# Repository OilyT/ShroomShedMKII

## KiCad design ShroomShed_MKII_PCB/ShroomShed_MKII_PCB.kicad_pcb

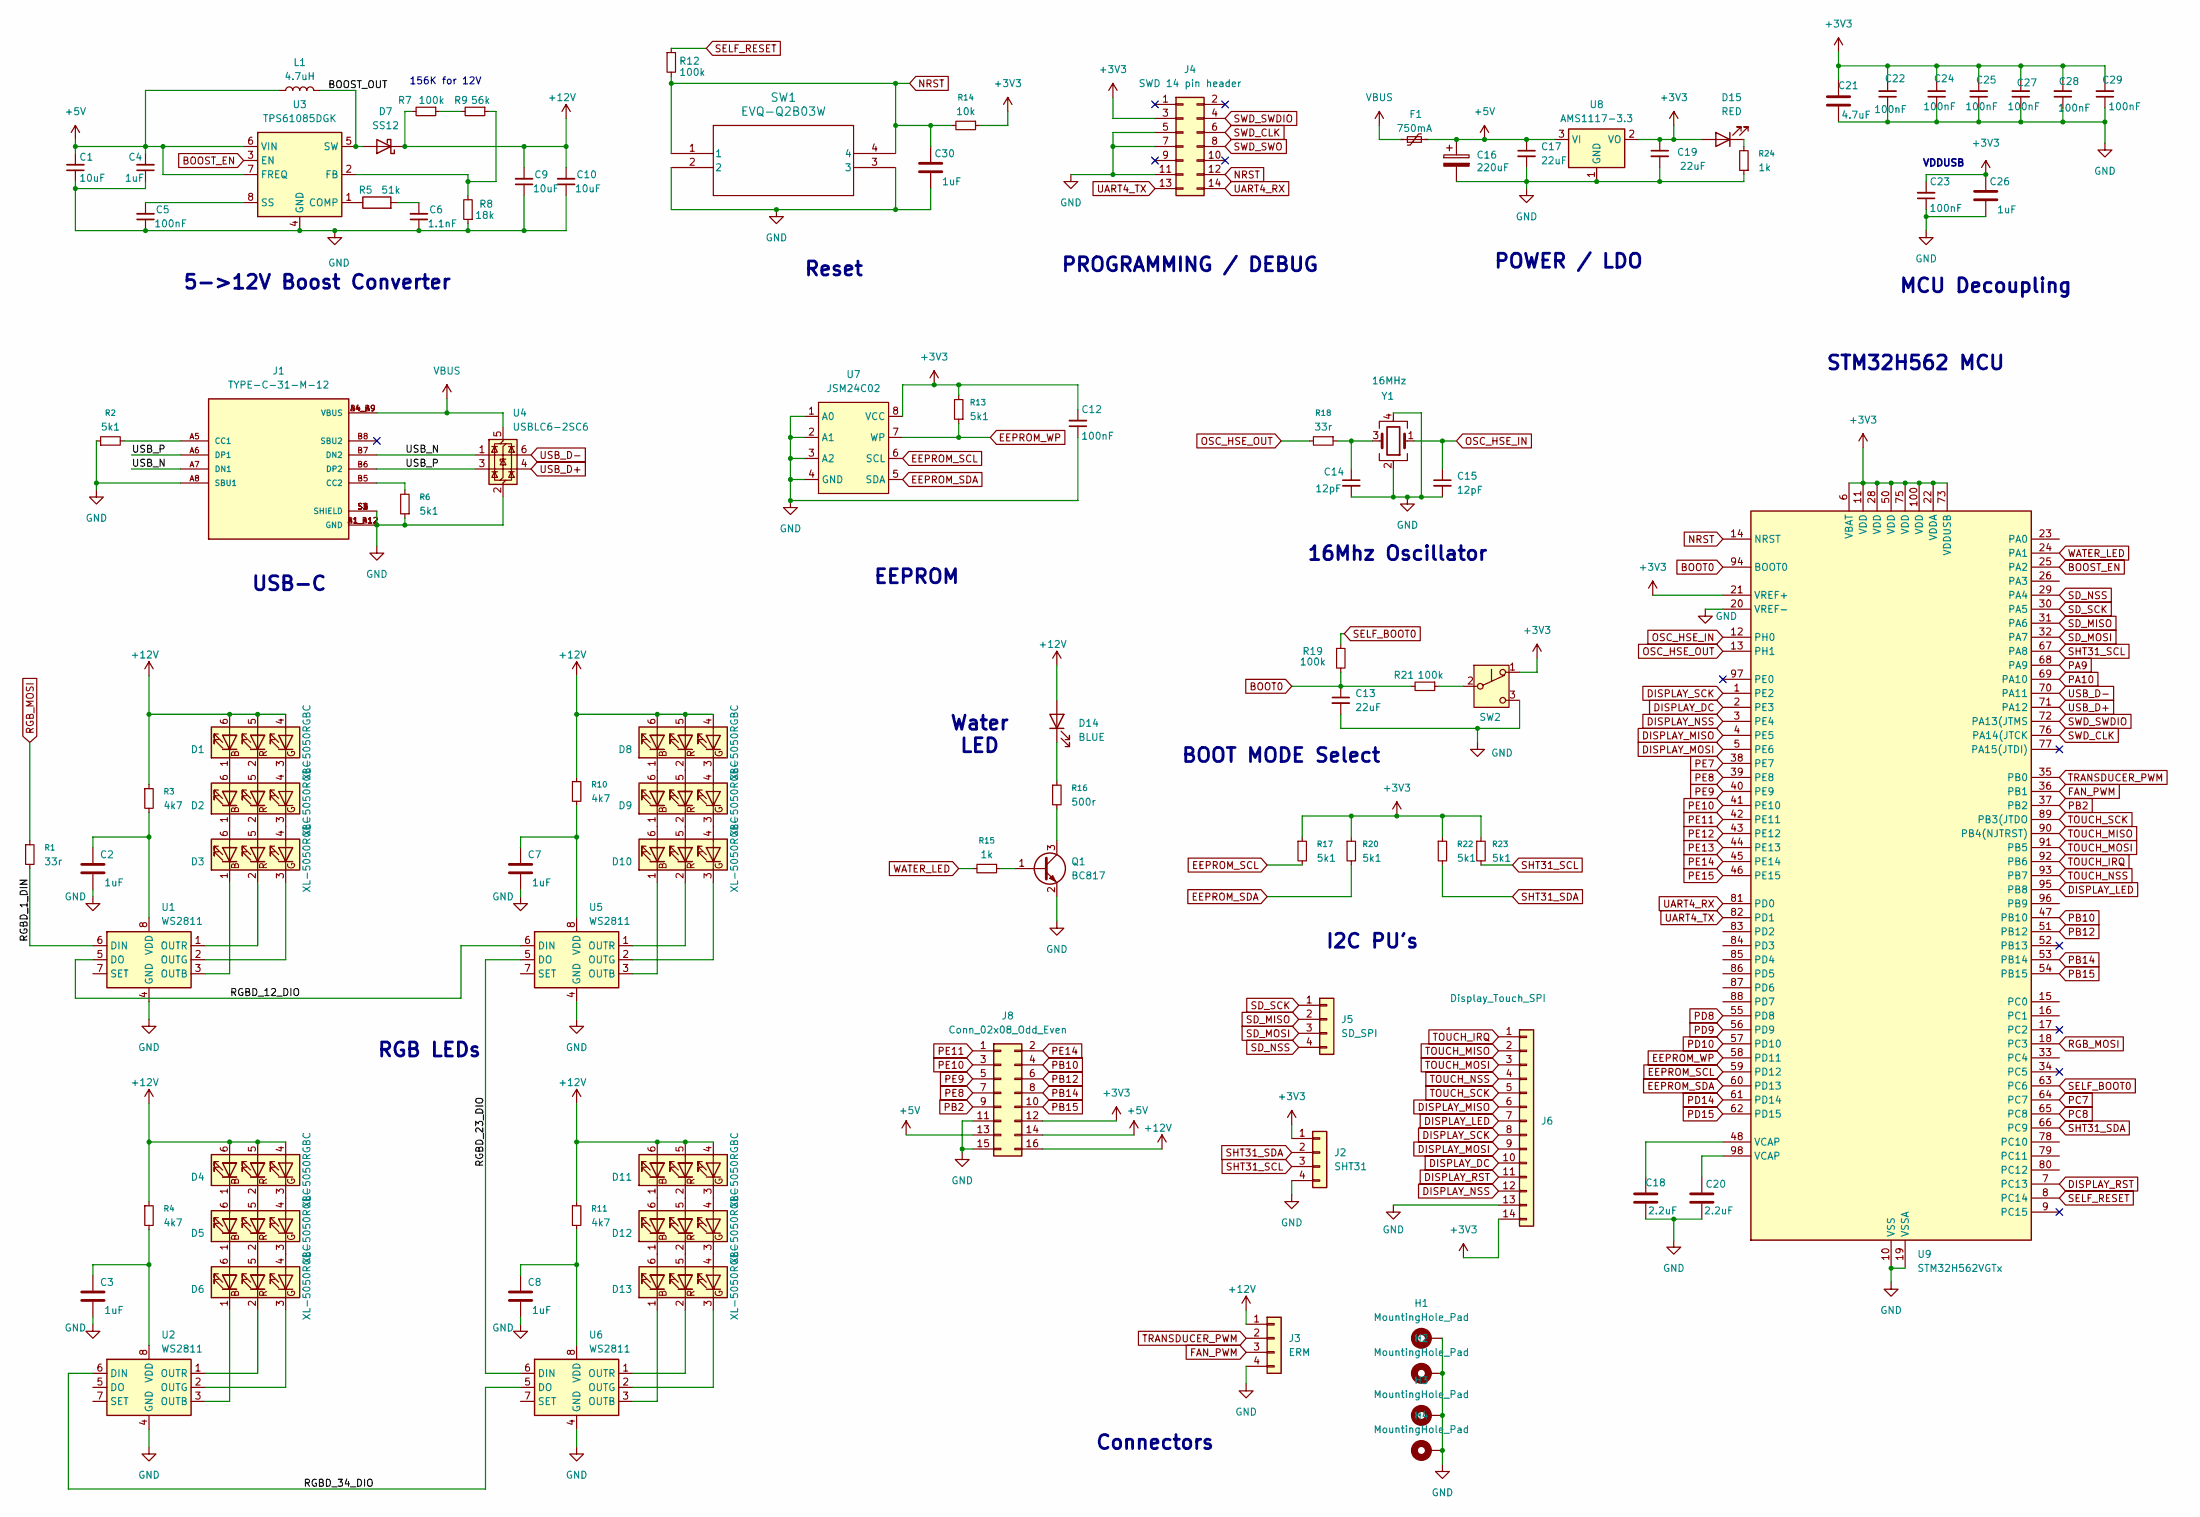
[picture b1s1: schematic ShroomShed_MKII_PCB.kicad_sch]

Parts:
C1, C9, C10: 10uF; C_0603_1608Metric
C2, C3, C4, C7, C8, C26, C30: 1uF; C_0603_1608Metric
C5, C12, C22, C23, C24, C25, C27, C28, C29: 100nF; C_0603_1608Metric
C6: 1.1nF; C_0603_1608Metric
C13, C17, C19: 22uF; C_0805_2012Metric
C14, C15: 12pF; C_0603_1608Metric
C16: 220uF; CP_Elec_6.3x5.4
C18, C20: 2.2uF; C_0603_1608Metric
C21: 4.7uF; C_0603_1608Metric
D1, D2, D3, D4, D5, D6, D8, D9, D10, D11, D12, D13: XL-5050RGBC; LED_RGB_5050-6
D7: SS12; D_SMA
D14: BLUE; LED_D4.0mm
D15: RED; LED_0603_1608Metric
F1: 750mA; Fuse_1210_3225Metric_Pad1.42x2.65mm_HandSolder
H1, H2, H3, H4: MountingHole_Pad; MountingHole_3.2mm_M3_Pad_Via
J1: TYPE-C-31-M-12; HRO_TYPE-C-31-M-12; PARTREV 2020.12.08
J2: SHT31; JST_XH_S4B-XH-A-1_1x04_P2.50mm_Horizontal; JLCPCB Part # C696092
J3: ERM; JST_XH_S4B-XH-A-1_1x04_P2.50mm_Horizontal; JLCPCB Part # C696092
J4: SWD 14 pin header; PinHeader_2x07_P1.27mm_Vertical_SMD
J5: SD_SPI; PinSocket_1x04_P2.54mm_Vertical; JLCPCB Part # C696092
J6: Display_Touch_SPI; PinSocket_1x14_P2.54mm_Vertical; JLCPCB Part # C505101
J8: Conn_02x08_Odd_Even; PinHeader_2x08_P2.54mm_Vertical
L1: 4.7uH; L_7.3x7.3_H4.5
Q1: BC817; SOT-23
R1, R18: 33r; R_0603_1608Metric
R2, R6, R13, R17, R20, R22, R23: 5k1; R_0603_1608Metric
R3, R4, R10, R11: 4k7; R_0603_1608Metric
R5: 51k; R_0603_1608Metric
R7, R12, R19, R21: 100k; R_0603_1608Metric
R8: 18k; R_0603_1608Metric
R9: 56k; R_0603_1608Metric
R14: 10k; R_0603_1608Metric
R15, R24: 1k; R_0603_1608Metric
R16: 500r; R_0603_1608Metric
SW1: EVQ-Q2B03W; EVQQ2_3_PAN
SW2: BOOT SELECT; MST-22D18G2 3J
U1, U2, U5, U6: WS2811; SOIC-8_3.9x4.9mm_P1.27mm
U3: TPS61085DGK; VSSOP-8_3x3mm_P0.65mm
U4: USBLC6-2SC6; SOT-23-6
U7: JSM24C02; SOIC-8_3.9x4.9mm_P1.27mm
U8: AMS1117-3.3; SOT-223-3_TabPin2
U9: STM32H562VGTx; LQFP-100_14x14mm_P0.5mm
Y1: 16MHz; Crystal_SMD_3225-4Pin_3.2x2.5mm; part# C13738

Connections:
+3V3: C12.2, C19.1, C21.1, C22.2, C23.2, C24.2, C25.2, C26.1, C27.2, C28.2, C29.2, D15.2 (A), J2.1, J4.3, J6.14, J8.12, R13.2, R14.1, R17.1, R20.1, R22.1, R23.1, SW2.1 (A), U7.8 (VCC), U8.2 (VO), U9.6 (VBAT), U9.11 (VDD), U9.21 (VREF+), U9.22 (VDDA), U9.28 (VDD), U9.50 (VDD), U9.73 (VDDUSB), U9.75 (VDD), U9.100 (VDD)
+5V: C1.2, C4.2, C16.1, C17.1, F1.2, J8.13, J8.14, L1.1, U3.6 (VIN), U3.7 (FREQ), U8.3 (VI)
+12V: C9.2, C10.2, D1.4 (BA), D1.5 (GA), D1.6 (RA), D4.4 (BA), D4.5 (GA), D4.6 (RA), D7.1 (K), D8.4 (BA), D8.5 (GA), D8.6 (RA), D11.4 (BA), D11.5 (GA), D11.6 (RA), D14.2 (A), J3.1, J8.16, R3.1, R4.1, R7.2, R10.1, R11.1
/BOOST_OUT: D7.2 (A), L1.2, U3.5 (SW)
/RGBD_1_DIN: R1.2, U1.6 (DIN)
/RGBD_12_DIO: U1.5 (DO), U5.6 (DIN)
/RGBD_23_DIO: U5.5 (DO), U6.6 (DIN)
/RGBD_34_DIO: U2.6 (DIN), U6.5 (DO)
/USB_N: J1.A7 (DN1), J1.B7 (DN2), U4.1 (I/O1)
/USB_P: J1.A6 (DP1), J1.B6 (DP2), U4.3 (I/O2)
BOOST_EN: U3.3 (EN), U9.25 (PA2)
BOOT0: C13.1, R19.2, R21.2, U9.94 (BOOT0)
DISPLAY_DC: J6.10, U9.2 (PE3)
DISPLAY_LED: J6.7, U9.95 (PB8)
DISPLAY_MISO: J6.6, U9.4 (PE5)
DISPLAY_MOSI: J6.9, U9.5 (PE6)
DISPLAY_NSS: J6.12, U9.3 (PE4)
DISPLAY_RST: J6.11, U9.7 (PC13)
DISPLAY_SCK: J6.8, U9.1 (PE2)
EEPROM_SCL: R17.2, U7.6 (SCL), U9.59 (PD12)
EEPROM_SDA: R20.2, U7.5 (SDA), U9.60 (PD13)
EEPROM_WP: R13.1, U7.7 (WP), U9.58 (PD11)
FAN_PWM: J3.3, U9.36 (PB1)
GND: C1.1, C2.2, C3.2, C4.1, C5.1, C6.1, C7.2, C8.2, C9.1, C10.1, C12.1, C13.2, C14.2, C15.2, C16.2, C17.2, C18.1, C19.2, C20.1, C21.2, C22.1, C23.1, C24.1, C25.1, C26.2, C27.1, C28.1, C29.1, C30.2, H1.1 (1_1), H2.1 (1_1), H3.1 (1_1), H4.1 (1_1), J1.A1_B12 (GND), J1.A8 (SBU1), J1.B1_A12 (GND), J1.S1 (SHIELD), J1.S2 (SHIELD), J1.S3 (SHIELD), J1.S4 (SHIELD), J2.4, J3.4, J4.5, J4.7, J4.11, J6.13, J8.11, J8.15, Q1.2 (E), R2.1, R6.1, R8.1, R24.1, SW1.2, SW1.3, SW2.3 (C), U1.4 (GND), U2.4 (GND), U3.4 (GND), U4.2 (GND), U5.4 (GND), U6.4 (GND), U7.1 (A0), U7.2 (A1), U7.3 (A2), U7.4 (GND), U8.1 (GND), U9.10 (VSS), U9.19 (VSSA), U9.20 (VREF-), U9.27 (VSS), U9.49 (VSS), U9.74 (VSS), U9.99 (VSS), Y1.2, Y1.4
NRST: C30.1, J4.12, R12.2, R14.2, SW1.1, SW1.4, U9.14 (NRST)
unnamed: C6.2, R5.2
unnamed: C14.1, R18.1, Y1.3
unnamed: C18.2, U9.48 (VCAP)
unnamed: C20.2, U9.98 (VCAP)
unnamed: D1.3 (BK), D2.4 (BA)
unnamed: D1.2 (GK), D2.5 (GA)
unnamed: D1.1 (RK), D2.6 (RA)
unnamed: D2.3 (BK), D3.4 (BA)
unnamed: D2.2 (GK), D3.5 (GA)
unnamed: D2.1 (RK), D3.6 (RA)
unnamed: D3.3 (BK), U1.2 (OUTG)
unnamed: D3.2 (GK), U1.1 (OUTR)
unnamed: D3.1 (RK), U1.3 (OUTB)
unnamed: D4.3 (BK), D5.4 (BA)
unnamed: D4.2 (GK), D5.5 (GA)
unnamed: D4.1 (RK), D5.6 (RA)
unnamed: D5.3 (BK), D6.4 (BA)
unnamed: D5.2 (GK), D6.5 (GA)
unnamed: D5.1 (RK), D6.6 (RA)
unnamed: D6.3 (BK), U2.2 (OUTG)
unnamed: D6.2 (GK), U2.1 (OUTR)
unnamed: D6.1 (RK), U2.3 (OUTB)
unnamed: D8.3 (BK), D9.4 (BA)
unnamed: D8.2 (GK), D9.5 (GA)
unnamed: D8.1 (RK), D9.6 (RA)
unnamed: D9.3 (BK), D10.4 (BA)
unnamed: D10.3 (BK), U5.2 (OUTG)
unnamed: D9.2 (GK), D10.5 (GA)
unnamed: D10.2 (GK), U5.1 (OUTR)
unnamed: D9.1 (RK), D10.6 (RA)
unnamed: D10.1 (RK), U5.3 (OUTB)
unnamed: D11.3 (BK), D12.4 (BA)
unnamed: D11.2 (GK), D12.5 (GA)
unnamed: D11.1 (RK), D12.6 (RA)
unnamed: D12.3 (BK), D13.4 (BA)
unnamed: D12.2 (GK), D13.5 (GA)
unnamed: D12.1 (RK), D13.6 (RA)
unnamed: D13.3 (BK), U6.2 (OUTG)
unnamed: D13.2 (GK), U6.1 (OUTR)
unnamed: D13.1 (RK), U6.3 (OUTB)
unnamed: D14.1 (K), R16.1
unnamed: D15.1 (K), R24.2
unnamed: J1.A5 (CC1), R2.2
unnamed: J1.B5 (CC2), R6.2
unnamed: Q1.1 (B), R15.1
unnamed: Q1.3 (C), R16.2
unnamed: R7.1, R9.2
unnamed: R21.1, SW2.2 (B)
unnamed: C2.1, R3.2, U1.8 (VDD)
unnamed: C3.1, R4.2, U2.8 (VDD)
unnamed: R5.1, U3.1 (COMP)
unnamed: R8.2, R9.1, U3.2 (FB)
unnamed: C5.2, U3.8 (SS)
unnamed: C7.1, R10.2, U5.8 (VDD)
unnamed: C8.1, R11.2, U6.8 (VDD)
OSC_HSE_IN: C15.1, U9.12 (PH0), Y1.1
OSC_HSE_OUT: R18.2, U9.13 (PH1)
PA9: U9.68 (PA9)
PA10: U9.69 (PA10)
PB2: J8.9, U9.37 (PB2)
PB10: J8.4, U9.47 (PB10)
PB12: J8.6, U9.51 (PB12)
PB14: J8.8, U9.53 (PB14)
PB15: J8.10, U9.54 (PB15)
PC7: U9.64 (PC7)
PC8: U9.65 (PC8)
PD8: U9.55 (PD8)
PD9: U9.56 (PD9)
PD10: U9.57 (PD10)
PD14: U9.61 (PD14)
PD15: U9.62 (PD15)
PE7: U9.38 (PE7)
PE8: J8.7, U9.39 (PE8)
PE9: J8.5, U9.40 (PE9)
PE10: J8.3, U9.41 (PE10)
PE11: J8.1, U9.42 (PE11)
PE12: U9.43 (PE12)
PE13: U9.44 (PE13)
PE14: J8.2, U9.45 (PE14)
PE15: U9.46 (PE15)
RGB_MOSI: R1.1, U9.18 (PC3)
SD_MISO: J5.2, U9.31 (PA6)
SD_MOSI: J5.3, U9.32 (PA7)
SD_NSS: J5.4, U9.29 (PA4)
SD_SCK: J5.1, U9.30 (PA5)
SELF_BOOT0: R19.1, U9.63 (PC6)
SELF_RESET: R12.1, U9.8 (PC14)
SHT31_SCL: J2.3, R23.2, U9.67 (PA8)
SHT31_SDA: J2.2, R22.2, U9.66 (PC9)
SWD_CLK: J4.6, U9.76 (PA14(JTCK)
SWD_SWDIO: J4.4, U9.72 (PA13(JTMS)
SWD_SWO: J4.8
TOUCH_IRQ: J6.1, U9.92 (PB6)
TOUCH_MISO: J6.2, U9.90 (PB4(NJTRST))
TOUCH_MOSI: J6.3, U9.91 (PB5)
TOUCH_NSS: J6.4, U9.93 (PB7)
TOUCH_SCK: J6.5, U9.89 (PB3(JTDO)
TRANSDUCER_PWM: J3.2, U9.35 (PB0)
UART4_RX: J4.14, U9.81 (PD0)
UART4_TX: J4.13, U9.82 (PD1)
USB_D+: U4.4 (I/O2), U9.71 (PA12)
USB_D-: U4.6 (I/O1), U9.70 (PA11)
VBUS: F1.1, J1.A4_B9 (VBUS), J1.B4_A9 (VBUS), U4.5 (VBUS)
WATER_LED: R15.2, U9.24 (PA1)

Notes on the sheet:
STM32H562 MCU
16Mhz Oscillator
USB-C
BOOT MODE Select
MCU Decoupling
5->12V Boost Converter
RGB LEDs
POWER / LDO
Water LED
I2C PU's
PROGRAMMING / DEBUG
Connectors
Reset
VDDUSB
EEPROM
156K for 12V

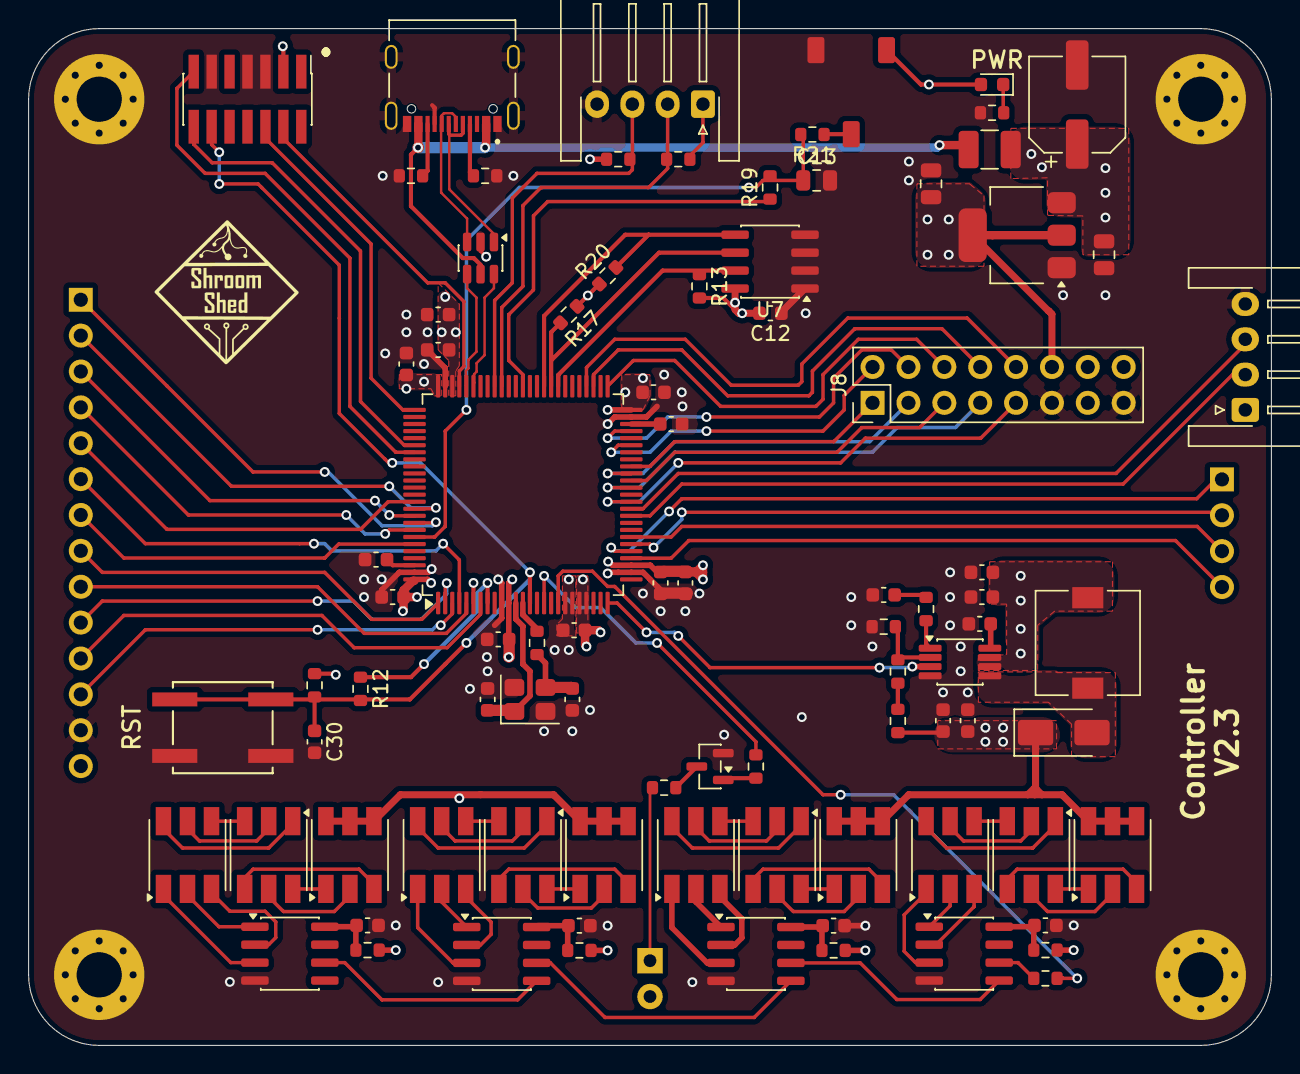
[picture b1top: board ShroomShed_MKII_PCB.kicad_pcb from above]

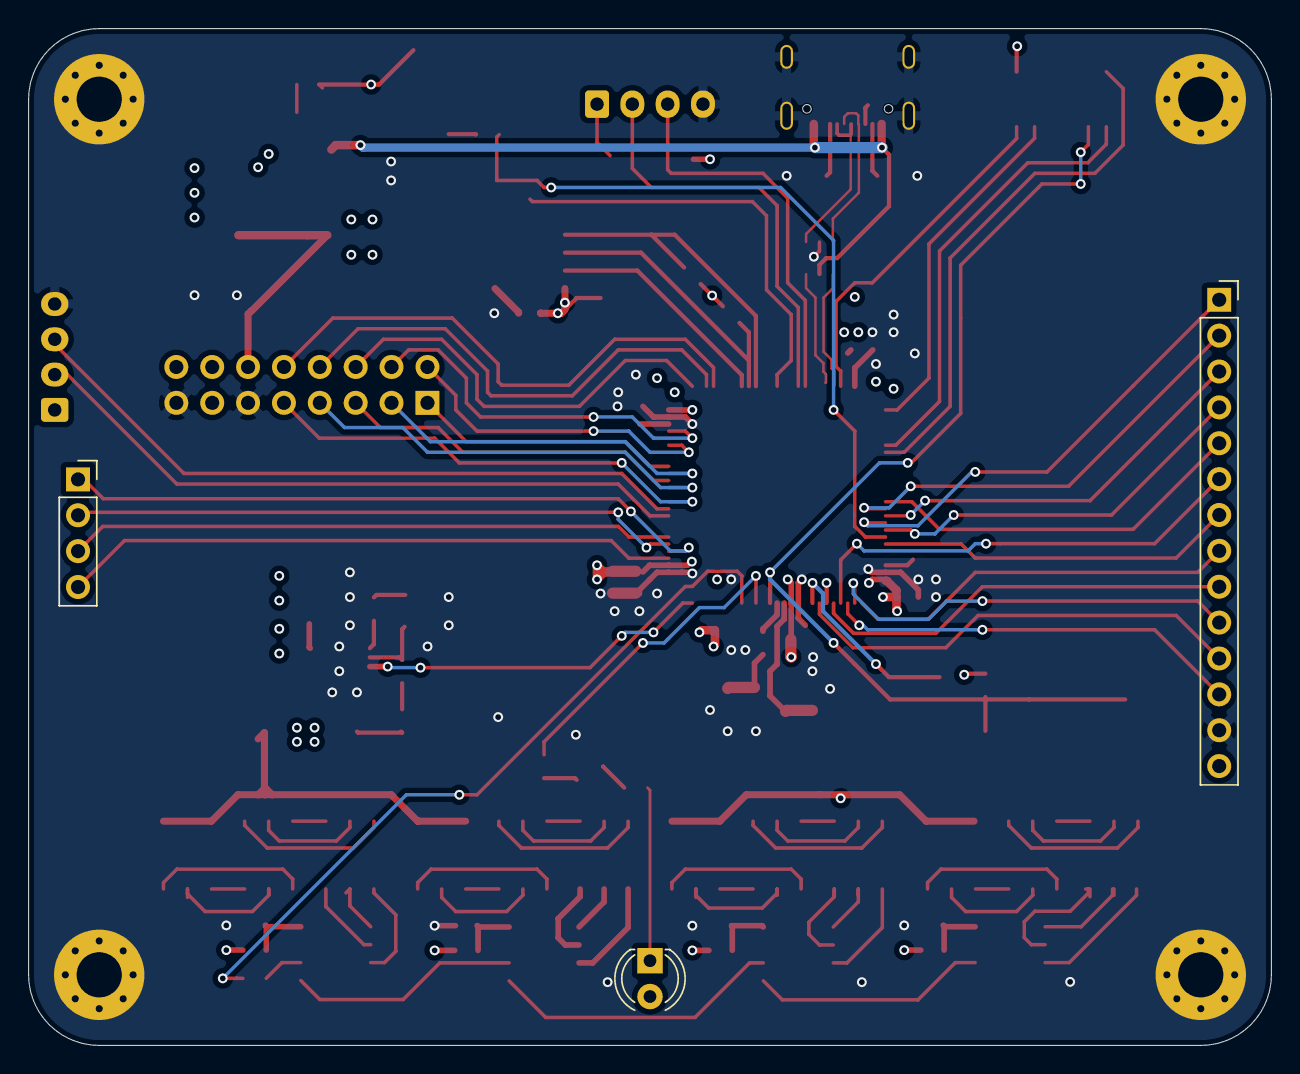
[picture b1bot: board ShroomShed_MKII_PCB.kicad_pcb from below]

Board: 4 copper layers, 88.0 x 72.0 mm, 94 parts (3 on the bottom side), 115 nets.

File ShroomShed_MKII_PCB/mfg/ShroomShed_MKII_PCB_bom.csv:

"Reference","Qty","Value","DNP","Exclude from BOM","Exclude from Board","Footprint","Datasheet","P#"
"C1,C9,C10","3","10uF","","","","Capacitor_SMD:C_0603_1608Metric","~",""
"C2,C3,C4,C7,C8,C25","6","1uF","","","","Capacitor_SMD:C_0603_1608Metric","~",""
"C5,C11,C12,C21,C22,C23,C24,C26,C27,C28","10","100nF","","","","Capacitor_SMD:C_0603_1608Metric","~",""
"C6","1","1.1nF","","","","Capacitor_SMD:C_0603_1608Metric","~",""
"C13,C14","2","12pF","","","","Capacitor_SMD:C_0603_1608Metric","~",""
"C15","1","470uF","","","","Capacitor_SMD:CP_Elec_6.3x7.7","","C2977552"
"C16,C17","2","22uF","","","","Capacitor_SMD:C_0805_2012Metric","~",""
"C18,C19","2","2.2uF","","","","Capacitor_SMD:C_0603_1608Metric","~",""
"C20","1","4.7uF","","","","Capacitor_SMD:C_0603_1608Metric","~",""
"D1,D2,D3,D4,D5,D6,D8,D9,D10,D11,D12,D13","12","XL-5050RGBC","","","","LED_SMD:LED_RGB_5050-6","~","C784540"
"D7","1","SS12","","","","Diode_SMD:D_SMA","https://www.vishay.com/docs/88746/ss12.pdf",""
"D14","1","BLUE","","","","LED_THT:LED_D4.0mm","~",""
"D15","1","RED","","","","LED_SMD:LED_0603_1608Metric","~",""
"F1","1","750mA","","","","Fuse:Fuse_1210_3225Metric_Pad1.42x2.65mm_HandSolder","~","C20805"
"H1,H2,H3,H4","4","MountingHole_Pad","","Excluded from BOM","","MountingHole:MountingHole_3.2mm_M3_Pad","~",""
"J1","1","TYPE-C-31-M-12","","","","footprints:HRO_TYPE-C-31-M-12","",""
"J2","1","UART","","","","Connector_PinHeader_2.00mm:PinHeader_1x04_P2.00mm_Vertical","~",""
"J3","1","Inputs","","","","Connector_JST:JST_XH_B6B-XH-A_1x06_P2.50mm_Vertical","~",""
"J4","1","SHT31","","","","Connector_JST:JST_XH_S4B-XH-A-1_1x04_P2.50mm_Horizontal","~",""
"J5","1","SWD 14 pin header","","","","Connector_PinHeader_1.27mm:PinHeader_2x07_P1.27mm_Vertical_SMD","~","C6332251"
"J6","1","ERM","","","","Connector_JST:JST_XH_S4B-XH-A-1_1x04_P2.50mm_Horizontal","~",""
"J7","1","SD_SPI","","","","Connector_PinSocket_2.54mm:PinSocket_1x04_P2.54mm_Vertical","~",""
"J8","1","Display_Touch_SPI","","","","Connector_PinSocket_2.54mm:PinSocket_1x14_P2.54mm_Vertical","~",""
"L1","1","4.7uH","","","","Inductor_SMD:L_7.3x7.3_H4.5","~",""
"Q1","1","BC817","","","","Package_TO_SOT_SMD:SOT-23","https://www.onsemi.com/pub/Collateral/BC818-D.pdf",""
"R1,R18","2","33r","","","","Resistor_SMD:R_0603_1608Metric","~",""
"R2,R6,R12,R13","4","5k1","","","","Resistor_SMD:R_0603_1608Metric","~",""
"R3,R4,R10,R11","4","4k7","","","","Resistor_SMD:R_0603_1608Metric","~",""
"R5","1","51k","","","","Resistor_SMD:R_0603_1608Metric","~",""
"R7","1","100k","","","","Resistor_SMD:R_0603_1608Metric","~",""
"R8","1","18k","","","","Resistor_SMD:R_0603_1608Metric","~",""
"R9","1","56k","","","","Resistor_SMD:R_0603_1608Metric","~",""
"R14,R17,R19,R20","4","10k","","","","Resistor_SMD:R_0603_1608Metric","~",""
"R15,R21","2","1k","","","","Resistor_SMD:R_0603_1608Metric","~",""
"R16","1","500r","","","","Resistor_SMD:R_0603_1608Metric","~",""
"SW1","1","EVQ-Q2B03W","","","","footprints:EVQQ2_3_PAN","EVQ-Q2B03W",""
"SW2","1","BOOT SELECT","","","","Button_Switch_SMD:SW_SPDT_Shouhan_MSK12C02","~","C431540"
"U1,U2,U5,U6","4","WS2811","","","","Package_SO:SOIC-8_3.9x4.9mm_P1.27mm","https://cdn-shop.adafruit.com/datasheets/WS2811.pdf",""
"U3","1","TPS61085DGK","","","","Package_SO:VSSOP-8_3x3mm_P0.65mm","https://www.ti.com/lit/ds/symlink/tps61085.pdf",""
"U4","1","USBLC6-2SC6","","","","Package_TO_SOT_SMD:SOT-23-6","https://www.st.com/resource/en/datasheet/usblc6-2.pdf",""
"U7","1","ENS210","","","","Package_DFN_QFN:AMS_QFN-4-1EP_2x2mm_P0.95mm_EP0.7x1.6mm","http://ams.com/eng/Products/Environmental-Sensors/Relative-H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",""
"U8","1","AMS1117-3.3","","","","Package_TO_SOT_SMD:SOT-223-3_TabPin2","http://www.advanced-monolithic.com/pdf/ds1117.pdf",""
"U9","1","STM32H562VGTx","","","","Package_QFP:LQFP-100_14x14mm_P0.5mm","https://www.st.com/resource/en/datasheet/stm32h562vg.pdf",""
"Y1","1","16MHz","","","","Crystal:Crystal_SMD_3225-4Pin_3.2x2.5mm","~",""

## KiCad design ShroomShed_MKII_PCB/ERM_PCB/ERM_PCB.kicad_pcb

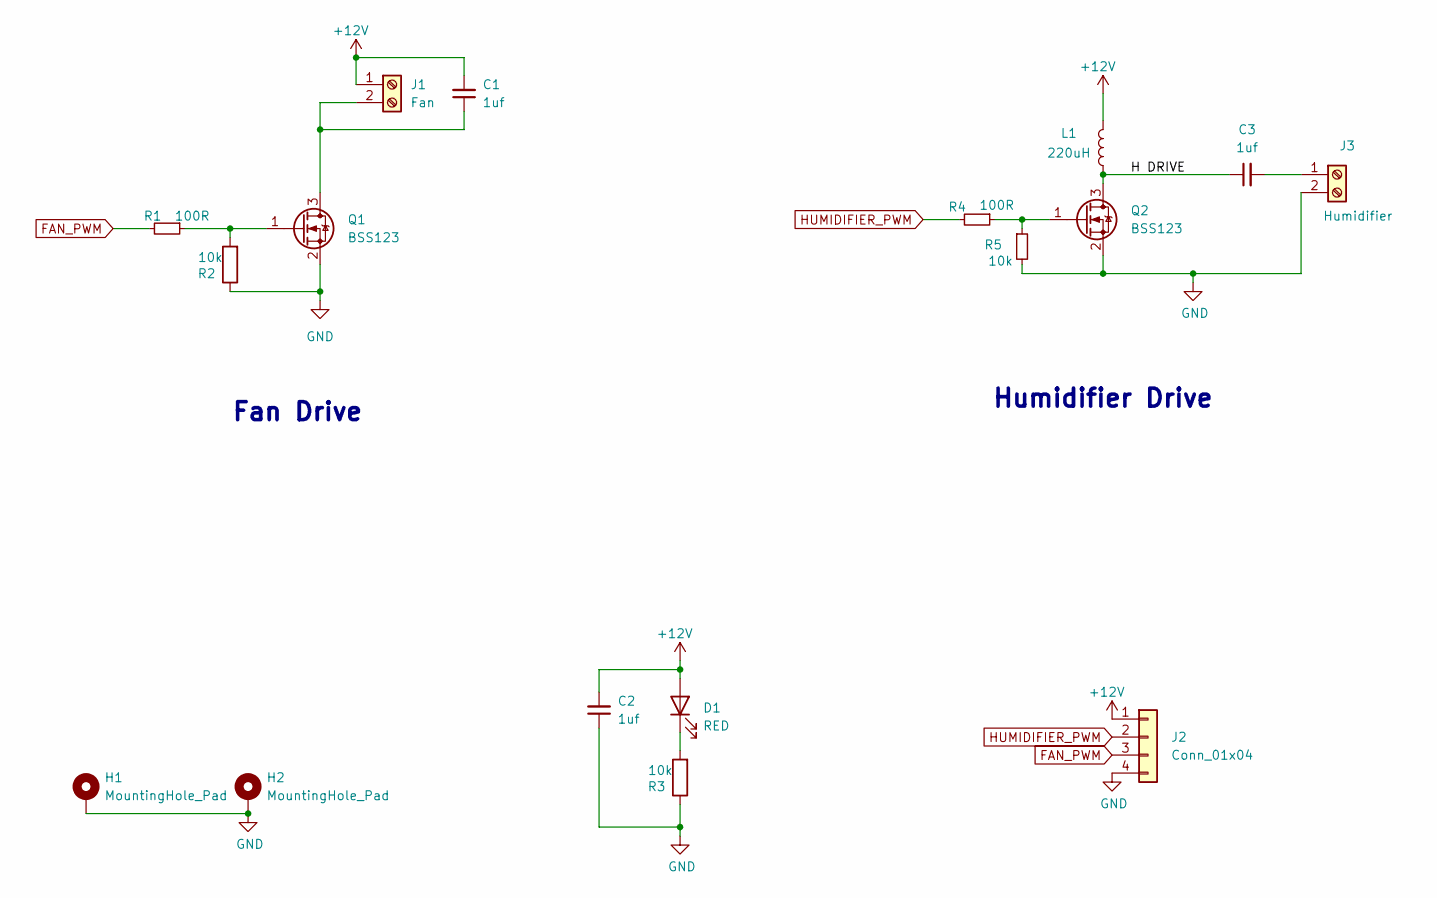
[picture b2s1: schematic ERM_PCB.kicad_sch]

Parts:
C1, C2, C3: 1uf; C_0603_1608Metric
D1: RED; LED_0603_1608Metric
H1, H2: MountingHole_Pad; MountingHole_3.2mm_M3_Pad
J1: Fan; JST_XH_S2B-XH-A-1_1x02_P2.50mm_Horizontal
J2: Conn_01x04; JST_XH_S4B-XH-A-1_1x04_P2.50mm_Horizontal
J3: Humidifier; JST_PH_S2B-PH-K_1x02_P2.00mm_Horizontal
L1: 220uH; SMDRH104R
Q1, Q2: BSS123; SOT-23
R1, R4: 100R; R_0603_1608Metric
R2, R3, R5: 10k; R_0603_1608Metric

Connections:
+12V: C1.2, C2.2, D1.2 (A), J1.1, J2.1, L1.2
/H DRIVE: C3.1, L1.1, Q2.3 (D)
FAN_PWM: J2.3, R1.2
GND: C2.1, H1.1 (1_1), H2.1 (1_1), J2.4, J3.2, Q1.2 (S), Q2.2 (S), R2.1, R3.1, R5.2
HUMIDIFIER_PWM: J2.2, R4.2
unnamed: D1.1 (K), R3.2
unnamed: C1.1, J1.2, Q1.3 (D)
unnamed: C3.2, J3.1
unnamed: Q1.1 (G), R1.1, R2.2
unnamed: Q2.1 (G), R4.1, R5.1

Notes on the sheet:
Humidifier Drive
Fan Drive

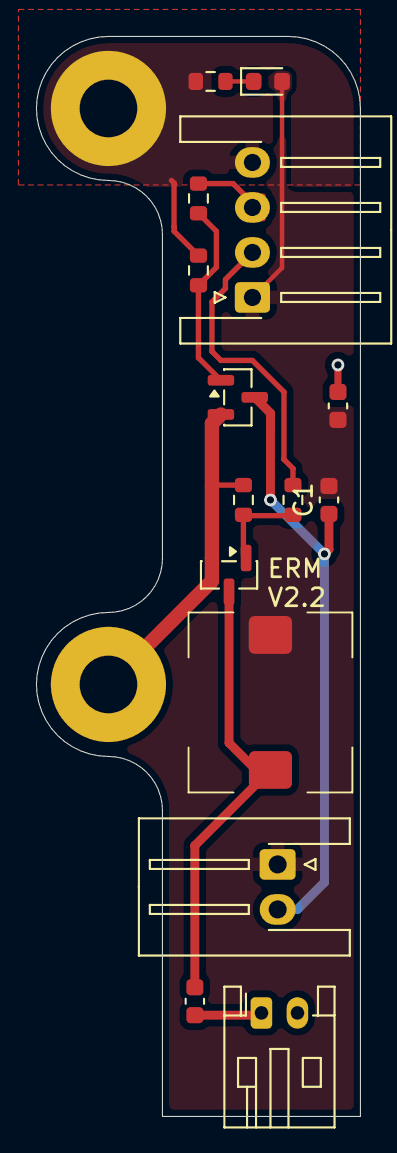
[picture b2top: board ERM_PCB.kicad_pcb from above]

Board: 2 copper layers, 18.0 x 60.0 mm, 17 parts (0 on the bottom side), 10 nets.

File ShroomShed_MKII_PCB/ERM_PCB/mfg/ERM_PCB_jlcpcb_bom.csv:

Comment,Designator,Footprint,JLCPCB Part #?optional?
1uf,"C1,C2",Capacitor_SMD:C_0603_1608Metric,
RED,D1,LED_SMD:LED_0603_1608Metric,
Fan,J1,Connector_JST:JST_XH_S2B-XH-A-1_1x02_P2.50mm_Horizontal,
Humidifier,J2,Connector_JST:JST_PH_S2B-PH-K_1x02_P2.00mm_Horizontal,
Conn_01x04,J3,Connector_JST:JST_XH_S4B-XH-A-1_1x04_P2.50mm_Horizontal,
220uH,L1,footprints:SMDRH104R,C3000009
BSS123,"Q1,Q2",Package_TO_SOT_SMD:SOT-23,C8491
100R,"R1,R3",Resistor_SMD:R_0603_1608Metric,
10k,"R2,R4,R5",Resistor_SMD:R_0603_1608Metric,

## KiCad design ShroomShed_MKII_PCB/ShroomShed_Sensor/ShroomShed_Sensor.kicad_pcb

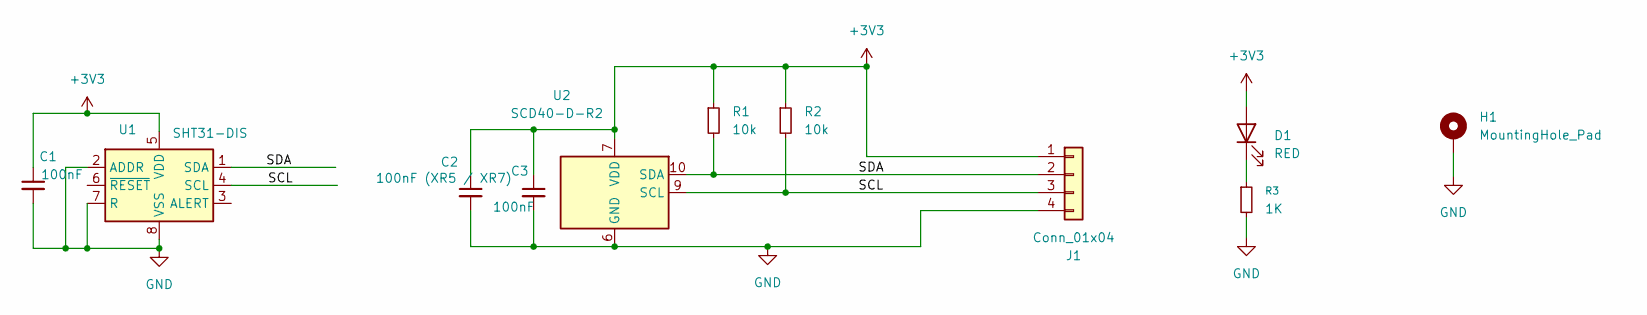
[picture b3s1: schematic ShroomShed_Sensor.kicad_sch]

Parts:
C1, C3: 100nF; C_0603_1608Metric
C2: 100nF (XR5 / XR7); C_0603_1608Metric
D1: RED; LED_0603_1608Metric
H1: MountingHole_Pad; MountingHole_3.2mm_M3_Pad
J1: Conn_01x04; JST_XH_B4B-XH-AM_1x04_P2.50mm_Vertical
R1, R2: 10k; R_0603_1608Metric
R3: 1K; R_0603_1608Metric
U1: SHT31-DIS; Sensirion_DFN-8-1EP_2.5x2.5mm_P0.5mm_EP1.1x1.7mm
U2: SCD40-D-R2; Sensirion_SCD4x-1EP_10.1x10.1mm_P1.25mm_EP4.8x4.8mm

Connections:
+3V3: C1.1, C2.1, C3.1, D1.2 (A), J1.1, R1.1, R2.1, U1.5 (VDD), U2.7 (VDD), U2.19 (VDD)
/SCL: J1.3, R2.2, U1.4 (SCL), U2.9 (SCL)
/SDA: J1.2, R1.2, U1.1 (SDA), U2.10 (SDA)
GND: C1.2, C2.2, C3.2, H1.1 (1_1), J1.4, R3.2, U1.2 (ADDR), U1.7 (R), U1.8 (VSS), U1.9 (VSS), U2.6 (GND), U2.20 (GND), U2.21 (GND)
unnamed: D1.1 (K), R3.1

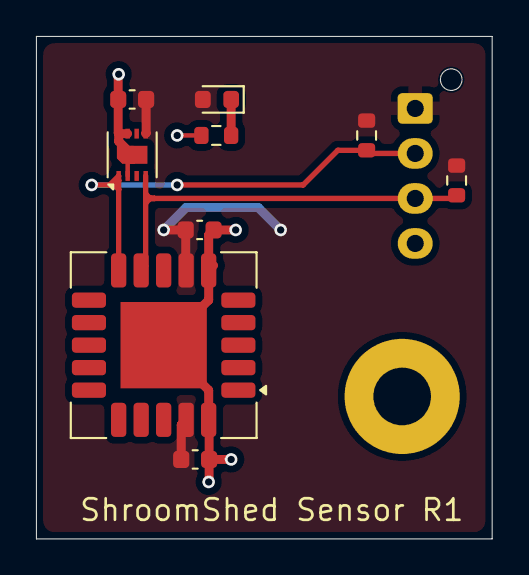
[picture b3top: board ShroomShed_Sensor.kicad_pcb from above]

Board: 2 copper layers, 25.3 x 27.9 mm, 11 parts (1 on the bottom side), 5 nets.

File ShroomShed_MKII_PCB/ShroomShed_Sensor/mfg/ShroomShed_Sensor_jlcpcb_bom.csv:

Comment,Designator,Footprint,JLCPCB Part #?optional?
100nF,"C1,C3",Capacitor_SMD:C_0603_1608Metric,
100nF (XR5 / XR7),C2,Capacitor_SMD:C_0603_1608Metric,
RED,D1,LED_SMD:LED_0603_1608Metric,
Conn_01x04,J1,Connector_JST:JST_XH_B4B-XH-AM_1x04_P2.50mm_Vertical,
10k,"R1,R2",Resistor_SMD:R_0603_1608Metric,
1K,R3,Resistor_SMD:R_0603_1608Metric,
SHT31-DIS,U1,Sensor_Humidity:Sensirion_DFN-8-1EP_2.5x2.5mm_P0.5mm_EP1.1x1.7mm,
SCD40-D-R2,U2,Sensor:Sensirion_SCD4x-1EP_10.1x10.1mm_P1.25mm_EP4.8x4.8mm,

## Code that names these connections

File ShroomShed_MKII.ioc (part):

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Mcu.Name=STM32H562VGTx
Mcu.Package=LQFP100
Mcu.UserName=STM32H562VGTx
PA1.GPIOParameters=GPIO_Label
PA1.GPIO_Label=WATER_LED
PA1.Signal=GPIO_Output
PA11.Mode=Device
PA11.Signal=USB_DM
PA12.Mode=Device
PA12.Signal=USB_DP
PA13(JTMS/SWDIO).Mode=Serial_Wire
PA13(JTMS/SWDIO).Signal=DEBUG_JTMS-SWDIO
PA14(JTCK/SWCLK).Mode=Serial_Wire
PA14(JTCK/SWCLK).Signal=DEBUG_JTCK-SWCLK
PA2.GPIOParameters=GPIO_Label
PA2.GPIO_Label=BOOST_EN
PA2.Signal=GPIO_Output
PA4.GPIOParameters=GPIO_Speed,PinState,GPIO_Label
PA4.GPIO_Label=SD_CS
PA4.GPIO_Speed=GPIO_SPEED_FREQ_VERY_HIGH
PA4.PinState=GPIO_PIN_SET
PA4.Signal=GPIO_Output
PA5.GPIOParameters=GPIO_Label
PA5.GPIO_Label=SD_SCK
PA5.Mode=Full_Duplex_Master
PA5.Signal=SPI6_SCK
PA6.GPIOParameters=GPIO_Label
PA6.GPIO_Label=SD_MISO
PA6.Mode=Full_Duplex_Master
PA6.Signal=SPI6_MISO
PA7.GPIOParameters=GPIO_Label
PA7.GPIO_Label=SD_MOSI
PA7.Mode=Full_Duplex_Master
PA7.Signal=SPI6_MOSI
PA8.GPIOParameters=GPIO_Label
PA8.GPIO_Label=SHT31_SCL
PA8.Mode=I2C
PA8.Signal=I2C3_SCL
PB0.GPIOParameters=GPIO_Label
PB0.GPIO_Label=TRANDUCER_PWM
PB0.Signal=S_TIM3_CH3
PB1.GPIOParameters=GPIO_Label
PB1.GPIO_Label=FAN_PWM
PB1.Mode=PWM Generation3 CH3N
PB1.Signal=TIM1_CH3N
PB13.Mode=TX_Only_Simplex_Unidirect_Master
PB13.Signal=SPI2_SCK
PB3(JTDO/TRACESWO).GPIOParameters=GPIO_Label
PB3(JTDO/TRACESWO).GPIO_Label=TOUCH_SCK
PB3(JTDO/TRACESWO).Mode=Full_Duplex_Master
PB3(JTDO/TRACESWO).Signal=SPI1_SCK
PB4(NJTRST).GPIOParameters=GPIO_Label
PB4(NJTRST).GPIO_Label=TOUCH_MISO
PB4(NJTRST).Mode=Full_Duplex_Master
PB4(NJTRST).Signal=SPI1_MISO
PB5.GPIOParameters=GPIO_Label
PB5.GPIO_Label=TOUCH_MOSI
PB5.Mode=Full_Duplex_Master
PB5.Signal=SPI1_MOSI
PB6.GPIOParameters=GPIO_Label,GPIO_ModeDefaultEXTI
PB6.GPIO_Label=TOUCH_IRQ
PB6.GPIO_ModeDefaultEXTI=GPIO_MODE_IT_RISING_FALLING
PB6.Signal=GPXTI6
PB7.GPIOParameters=GPIO_Speed,PinState,GPIO_Label
PB7.GPIO_Label=TOUCH_CS
PB7.GPIO_Speed=GPIO_SPEED_FREQ_VERY_HIGH
PB7.PinState=GPIO_PIN_SET
PB7.Signal=GPIO_Output
PB8.GPIOParameters=GPIO_Label
PB8.GPIO_Label=DISPLAY_LED
PB8.Signal=S_TIM4_CH3
PC13.GPIOParameters=GPIO_Speed,PinState,GPIO_PuPd,GPIO_Label
PC13.GPIO_Label=DISPLAY_RST
PC13.GPIO_PuPd=GPIO_PULLUP
PC13.GPIO_Speed=GPIO_SPEED_FREQ_LOW
PC13.PinState=GPIO_PIN_SET
PC13.Signal=GPIO_Output
PC14-OSC32_IN(OSC32_IN).GPIOParameters=GPIO_Label
PC14-OSC32_IN(OSC32_IN).GPIO_Label=SELF_RESET
PC14-OSC32_IN(OSC32_IN).Signal=GPIO_Output
PC3.GPIOParameters=GPIO_Speed,GPIO_PuPd,GPIO_Label
PC3.GPIO_Label=RGB_MOSI
PC3.GPIO_PuPd=GPIO_PULLDOWN
PC3.GPIO_Speed=GPIO_SPEED_FREQ_HIGH
PC3.Mode=TX_Only_Simplex_Unidirect_Master
PC3.Signal=SPI2_MOSI
PC6.GPIOParameters=GPIO_Label
PC6.GPIO_Label=SELF_BOOT0
PC6.Signal=GPIO_Output
PC9.GPIOParameters=GPIO_Label
PC9.GPIO_Label=SHT31_SDA
PC9.Mode=I2C
PC9.Signal=I2C3_SDA
PD0.Mode=Asynchronous
PD0.Signal=UART4_RX
PD1.Mode=Asynchronous
PD1.Signal=UART4_TX
PD11.GPIOParameters=GPIO_Label
PD11.GPIO_Label=EEPROM_WP
PD11.Signal=GPIO_Output
PD12.GPIOParameters=GPIO_Label
PD12.GPIO_Label=EEPROM_SCL
PD12.Mode=I2C
PD12.Signal=I2C4_SCL
PD13.GPIOParameters=GPIO_Label
PD13.GPIO_Label=EEPROM_SDA
PD13.Mode=I2C
PD13.Signal=I2C4_SDA
PE2.GPIOParameters=GPIO_Speed,GPIO_PuPd,GPIO_Label,GPIO_Mode
PE2.GPIO_Label=DISPLAY_SCK
PE2.GPIO_Mode=GPIO_MODE_AF_PP
PE2.GPIO_PuPd=GPIO_PULLDOWN
PE2.GPIO_Speed=GPIO_SPEED_FREQ_VERY_HIGH
PE2.Mode=Full_Duplex_Master
PE2.Signal=SPI4_SCK
PE3.GPIOParameters=GPIO_Speed,PinState,GPIO_PuPd,GPIO_Label,GPIO_ModeDefaultOutputPP
PE3.GPIO_Label=DISPLAY_DC
PE3.GPIO_ModeDefaultOutputPP=GPIO_MODE_OUTPUT_PP
PE3.GPIO_PuPd=GPIO_NOPULL
PE3.GPIO_Speed=GPIO_SPEED_FREQ_VERY_HIGH
PE3.PinState=GPIO_PIN_RESET
PE3.Signal=GPIO_Output
PE4.GPIOParameters=GPIO_Speed,PinState,GPIO_Label
PE4.GPIO_Label=DISPLAY_CS
PE4.GPIO_Speed=GPIO_SPEED_FREQ_VERY_HIGH
PE4.PinState=GPIO_PIN_SET
PE4.Signal=GPIO_Output
PE5.GPIOParameters=GPIO_Label
PE5.GPIO_Label=DISPLAY_MISO
PE5.Mode=Full_Duplex_Master
PE5.Signal=SPI4_MISO
PE6.GPIOParameters=GPIO_Speed,PinState,GPIO_PuPd,GPIO_Label,GPIO_ModeDefaultOutputPP
PE6.GPIO_Label=DISPLAY_MOSI
PE6.GPIO_ModeDefaultOutputPP=GPIO_MODE_OUTPUT_PP
PE6.GPIO_PuPd=GPIO_PULLUP
PE6.GPIO_Speed=GPIO_SPEED_FREQ_VERY_HIGH
PE6.Mode=Full_Duplex_Master
PE6.PinState=GPIO_PIN_RESET
PE6.Signal=SPI4_MOSI
PH0-OSC_IN(PH0).Mode=HSE-External-Oscillator
PH0-OSC_IN(PH0).Signal=RCC_OSC_IN
PH1-OSC_OUT(PH1).Mode=HSE-External-Oscillator
PH1-OSC_OUT(PH1).Signal=RCC_OSC_OUT
RCC.HSE_VALUE=16000000
RCC.SYSCLKFreq_VALUE=250000000
RCC.SYSCLKSource=RCC_SYSCLKSOURCE_PLLCLK
board=custom

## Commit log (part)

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2026-01-16 added solidworks files
2026-02-02 controller 2.0 commit
2026-02-02 removed corrupted sldprt
2026-02-02 source code template setup and blinky achieved
2026-02-03 completed new ERM (solidworks + PCB) solidworks Frame complete
2026-02-06 finished V2.1 PCB
2026-02-11 got the display working thank fuck
2026-02-11 display now working properly, sort of
2026-02-11 improved implementation of draw rectangle functiom
2026-02-12 implemented LVGL / EEZ flush callback not quite working properly
2026-02-13 got sht31 library working, had to FIX THE DOGHSHIT RETARDED INTERFACE TEMPLATE
2026-02-16 imlemented SCD40 driver and Api
2026-02-19 got usb to serial printing working
2026-02-19 solidworks assembly all main dimensions now changable
2026-02-20 added stuff like touch and stuff and humidifier control
2026-02-23 touchscreen fully integrated, basic humidity and airflow control now functional from display
2026-02-23 finished 0.1 basic UI, improved touch button press sensitivity
2026-02-25 adapted for V2.1 controller
2026-02-26 RGB LED driver fully functional with disco mode
2026-02-26 improved UI responsiveness, also improved disco mode
2026-02-27 new disco mode control screen and begun integration of interupts for touch screen detection
2026-02-27 improved touch implementation with buffer, abandoned interrupts since that was a shit idea and just fucked verything up
2026-03-02 fan PWMM now functional
2026-03-05 updated soldiworks to first full 2.0 MKII configuration, added SD driver (not tested)
2026-03-06 working on improved touch driver, need to fix transmit receive bit synch / timings
2026-03-09 implemented shroomshedV1 low water level detection and DHT heater process
2026-03-09 humidity CV now able to be changed either +1 or +10
2026-03-09 implemented main menu and general settings page with display brightness
2026-03-09 dickinbaus
2026-03-11 additions to UI + humidity PID controller now tuned properly
2026-03-16 got 18bit rgb working, now need to use DMA controller as significantly slower than before
2026-03-18 completed controler V2.2, got basic blocking implementation of display SPI DMA working
2026-03-24 Fixed distance between display pin headers, checkpoint for proper DMA implementation
2026-04-01 updated cad
2026-04-01 increased rgb speed constant
2026-04-01 penis
2026-04-01 added mushroom source files (WIP)
2026-04-03 more stuff
2026-04-09 fixed a beug
2026-04-28 Controller V2.2 ordered
2026-04-29 saving checkpoint before fucking with frame cad
2026-04-29 Initital frame update commit, seem ok so far
2026-04-29 checkpoint before I fugg up the whole assembly to fix the equations
2026-04-29 cad model updated and not broken, still need to export manufcatoring files for laser
